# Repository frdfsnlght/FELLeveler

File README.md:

# FELLeveler
An electronic leveler for a tractor front end loader.

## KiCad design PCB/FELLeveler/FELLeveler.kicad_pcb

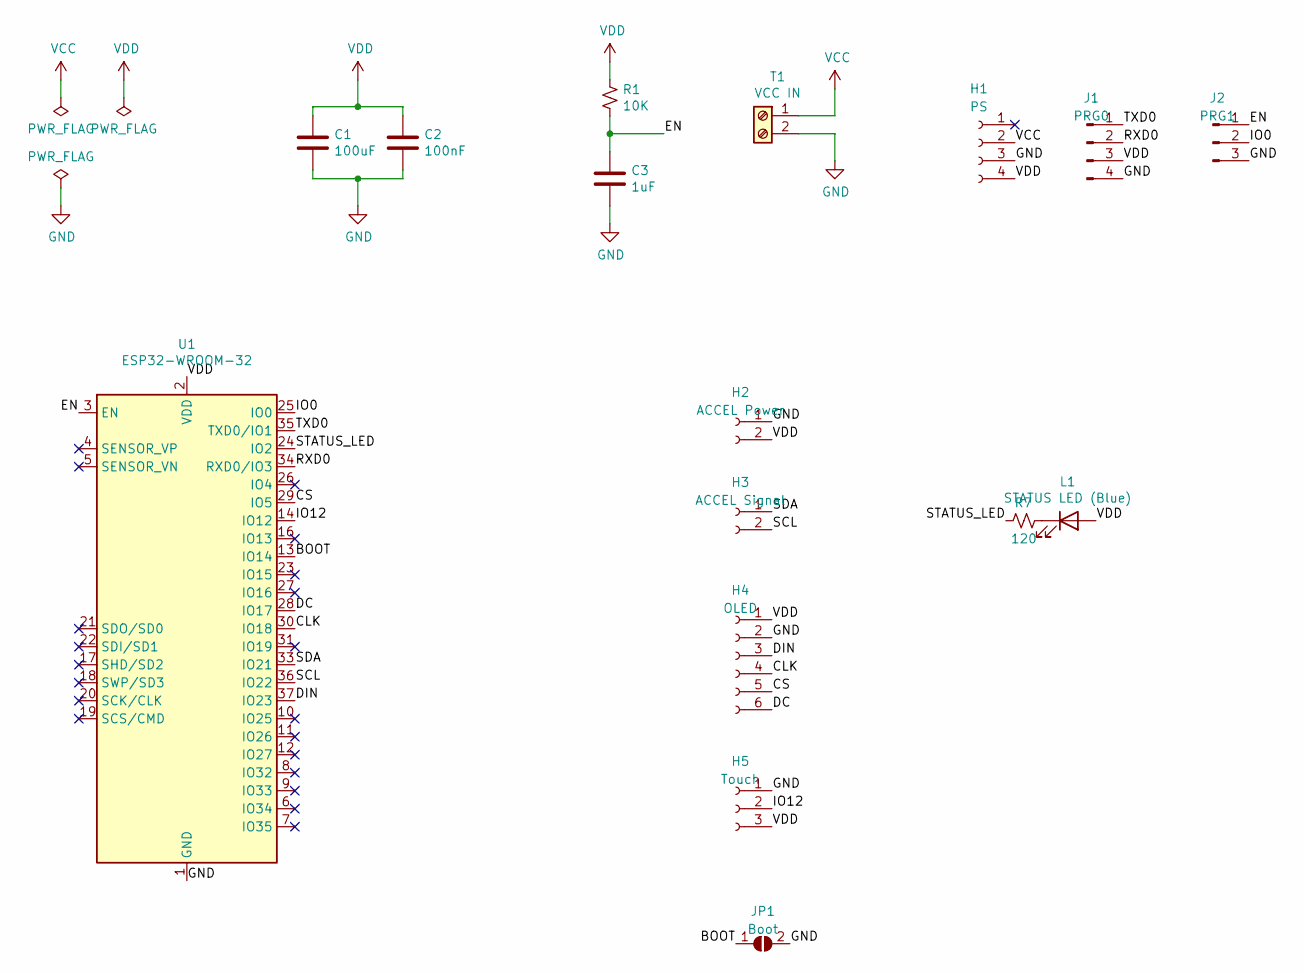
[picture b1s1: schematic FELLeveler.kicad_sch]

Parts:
C1: 100uF; C_1206_3216Metric
C2: 100nF; C_0805_2012Metric
C3: 1uF; C_0805_2012Metric
H1: PS; PinSocket_1x04_P2.54mm_Horizontal
H2: ACCEL Power; PinSocket_1x02_P2.54mm_Horizontal
H3: ACCEL Signal; PinSocket_1x02_P2.54mm_Horizontal
H4: OLED; PinSocket_1x06_P2.54mm_Vertical
H5: Touch; PinSocket_1x03_P2.54mm_Vertical
J1: PRG0; PinHeader_1x04_P2.54mm_Vertical
J2: PRG1; PinHeader_1x03_P2.54mm_Vertical
JP1: Boot; SolderJumper-2_P1.3mm_Open_Pad1.0x1.5mm
L1: STATUS LED (Blue); LED_0805_2012Metric
R1: 10K; R_0805_2012Metric
R7: 120; R_0805_2012Metric
T1: VCC IN; Screw_Terminal_2_P3.5_Horizontal
U1: ESP32-WROOM-32

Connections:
/BOOT: JP1.1 (A), U1.13 (IO14)
/CLK: H4.4, U1.30 (IO18)
/CS: H4.5, U1.29 (IO5)
/DC: H4.6, U1.28 (IO17)
/DIN: H4.3, U1.37 (IO23)
/EN: C3.1, J2.1, R1.2, U1.3 (EN)
/IO0: J2.2, U1.25 (IO0)
/IO12: H5.2, U1.14 (IO12)
/RXD0: J1.2, U1.34 (RXD0/IO3)
/SCL: H3.2, U1.36 (IO22)
/SDA: H3.1, U1.33 (IO21)
/STATUS_LED: R7.1, U1.24 (IO2)
/TXD0: J1.1, U1.35 (TXD0/IO1)
GND: C1.2, C2.2, C3.2, H1.3, H2.1, H4.2, H5.1, J1.4, J2.3, JP1.2 (B), T1.2, U1.1 (GND), U1.15 (GND), U1.38 (GND), U1.39 (GND)
unnamed: L1.1 (K), R7.2
VCC: H1.2, T1.1
VDD: C1.1, C2.1, H1.4, H2.2, H4.1, H5.3, J1.3, L1.2 (A), R1.1, U1.2 (VDD)

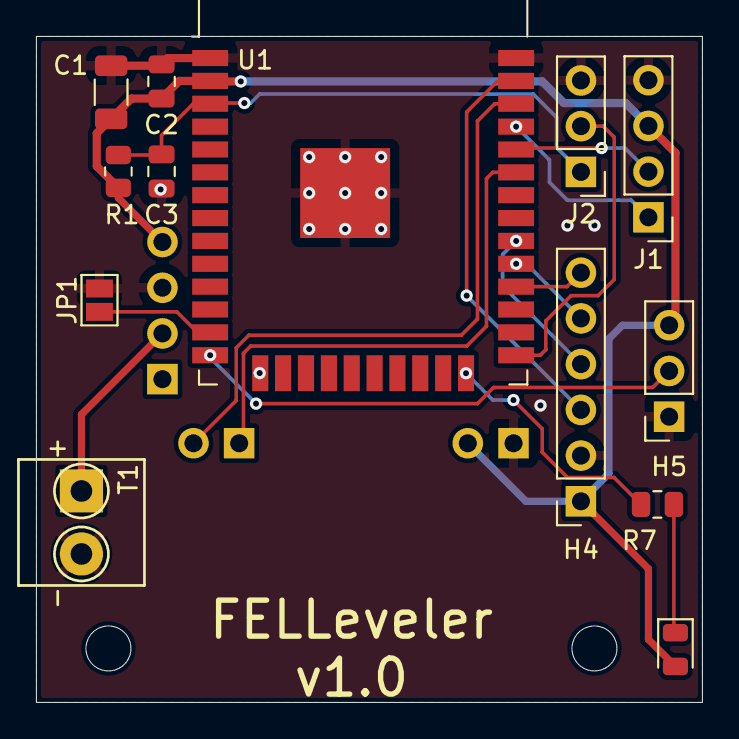
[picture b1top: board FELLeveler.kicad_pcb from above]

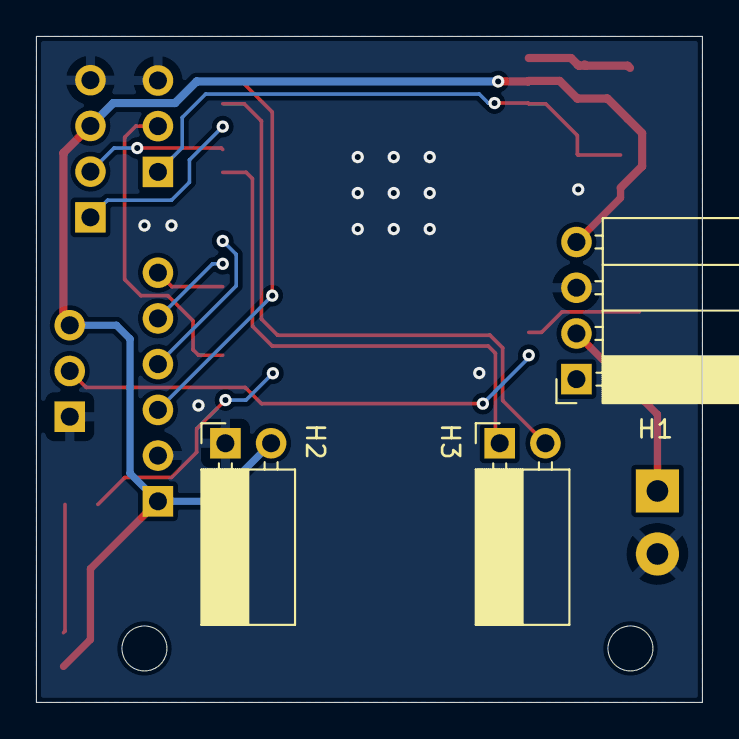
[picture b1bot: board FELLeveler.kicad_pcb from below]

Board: 2 copper layers, 37.0 x 37.0 mm, 16 parts (3 on the bottom side), 17 nets.

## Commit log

2022-06-27 More code
2022-07-06 Started webapp
2022-07-10 First test version
2022-07-12 Changed
2022-07-16 More changes
2022-07-18 About to switch to web sockets
2022-07-19 Sort of working websockets
2022-07-25 New SockIO protocol
2022-07-27 Feature complete version
2022-08-01 Working version
2022-08-01 Started PCB design
2022-08-03 Initial positioning
2022-08-03 PCB routed
2022-08-04 Added Boot pin, tweaked PCB
2022-08-05 Tweaked PCB, submitted v1.0 to fab.
2022-08-08 Rotated display and added ability to invert pitch axis.
2022-08-08 Started 3D part design
2022-08-09 Started box base part
2022-08-16 Added custom image format and generator
2022-08-16 Work on mounting bracket
2022-08-16 Started to add decoder for new image format.
2022-08-16 First complete implementation of new image format
2022-08-16 Finished box mount
2022-08-18 Fixed up
2022-08-18 Tweaked boot image, fixed Android WiFi connection, now 100% functional.
2022-08-18 Added message when serving "not found"
2022-08-18 Changed debug level to "info"
2022-08-19 Fixed Wifi reconnect
2022-08-20 First version of many of the parts, will still need tweeking
2022-09-03 Tweaked 3D parts
